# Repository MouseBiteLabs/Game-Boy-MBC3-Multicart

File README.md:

# Game Boy MBC3 Multicart

This is my design of a flashable MBC3-based multicart for the Game Boy. You can make a 2-in-1 or 4-in-1 cartridge, that changes games based on a button press or power cycling the Game Boy. With this board you can also make a single game, but with the addition of a pressable reset button on the cartridge.

The features are as follows:

- Able to make a cartridge with either 2x 2 MB games or 4x 1 MB games
- Adds a pressable button to the cartridge (no shell cutting required)
  - The button can be configured to cycle games on the cart, reset the console, or both
- Configurable to have separate save data for each game, or to share the same save data across multiple games
- Fully compatible with the <a href="https://www.gbxcart.com/">GBxCart RW</a> so you can transfer games and save files to and from the board

Some examples of fun cartridges you can make with this board are:
- A single Pokemon game that has a reset button
- Both Pokemon Gold and Silver with separate saves
- Both Pokemon Gold and Silver with *the same* save (save files are compatible between versions!)
- Both Pokemon Gold and Silver with *the same* save that can switch between versions *during gameplay without resetting* (hotswap!)
- A single copy of Mary-Kate and Ashley - Pocket Planner with two separate save files

All gerbers and source files can be found in this repo, as this project is fully open source. Technical documentation of the board can be found in the Technical folder.

## Tutorial Video

Here's a video companion to this repository, but you will still need to read the repo to complete the build.

")

## Important Things Before You Start

The most important thing to note is that SW2A MUST be in the OFF position. The board is still fully functional as long as you rely on the button inside the cartridge to switch games. **You cannot cycle games by turning the power on and off.** Details are below.

1) To use this board, you need to have an original Game Boy game that uses an MBC3 mapper chip. <a href="https://catskull.net/gb-rom-database/">You can find a list of games and their mappers here</a>. Use the search function. Please note the RAM is in bytes, not bits. Since SRAM in this repo is defined in bits, you need to convert by multiplying the number of bytes by 8.
2) You will need to remove the MBC3 from your donor cartridge for use on this board. This will require a hot air rework station or a hot plate. There's a list below of other parts you can re-use from the donor cartridge.
3) When soldering parts on, it's a good idea to put kapton tape or otherwise cover the bottom cartridge edge. You do not want to get solder on the cartridge contacts.
4) I am not responsible for any damage you do to your self or your property. Attempt this project at your own risk.
5) I do not guarantee design compatibility. You may encounter issues with certain games. There is also a chance I have made an error in the design or the BOM - if this is the case, I will do everything I can to address the problem as quickly as possible.
6) If you are using this board to make games other than for personal use, you must have permission from the originator to use and distribute any ROM images or other related material. You are responsible for making sure you adhere to any license requirements.

DO NOT use my circuit boards for profiting from stolen work - this especially includes homebrew content, ROM hacks, and using fan-made labels without permission from the originator. **Support original creators!**

## Board Characteristics and Order Information

The zipped folder contains all the gerber files for this board. The following options **must** be chosen when ordering boards for yourself.

- Thickness: 0.8mm
- Surface Finish: ENIG
- Gold Fingers: Yes, 30° chamfer

**Add this note to orders:** "The milling.gbr layer indicates where an unplated slot should be added to the board. Please add an unplated slot as indicated."

You can use the zipped folder at any board fabricator you like. You may also buy the board from PCBWay using this link (disclosure: I receive 10% of the sale value to go twoards future PCB orders of my own):

<a href="https://oshpark.com/shared_projects/9DCMXwOu">The board is also listed on OSH Park as well.</a> **Be sure to get them in 0.8mm thickness if you order from here.**

### Purchase from My Website

You can purchase this circuit board at my website, [https://mousebitelabs.store](https://mousebitelabs.store). Click the following image to be directed to the specific item listing:

### Purchase from Etsy

I also offer the board on Etsy, if you would rather purchase through there - click the banner to be redirected.

## Required Equipment

The EEPROMs on the board needs to be programmed somehow. I recommend using the GBxCart, as mentioned. These boards are fully compatible with it, and it makes reflashing games extremely easy using <a href="https://github.com/lesserkuma/FlashGBX">lesserkuma's FlashGBX software</a>.

Alternatively, you can buy an EEPROM programmer with a TSOP adapter. The downside to this method is that you have to desolder the chip every time you want to program it. The <a href="https://flashcatusb.com/">FlashcatUSB</a> is one popular option in retro spaces.

## Battery Safety

When assembling a board, I recommend populating all the parts *except* the battery, and getting it to run initially without it. This is to make it easier to fix any solder connections that might need fixing, without having to worry about getting the battery hot. And if you need to rework anything near the battery after you've put it on the board, be safe and remove it before putting a hot soldering iron next to it.

And this should go without saying, but if you're assembling these boards with a hot plate or hot air, *do not* solder the battery on this way. You should use an iron, and keep heat off of the battery as much as possible. 

(Also check polarity!)

## Board Configurations

There's a lot to cover here. There are four separate switches to configure, and two different sizes of SRAM to pick from. You also can add a real-time clock to the cartridge for games that needed it.

*Note that you can simply solder bridges from the middle pads of the switches to the left or right to the "ON" or "OFF" positions, instead of installing an actual switch.*

### Real-Time Clock (RTC)

If your game uses an RTC, populate C2, R2, X1, and Z1 as indicated in the BOM.

If your game does *not* use the RTC function, you can omit these parts, but you also need to bridge the pads of Z1 with solder.

### SRAM Size Selection

There are two sizes of SRAM you can use, and the type you use will dictate how your save data is stored on the cartridge and if it's shared between games or not.

- If you use a 1 Mbit SRAM (like the AS6C1008), then each game you put on the cartridge will have its own separate save files. If you program multiple copies of the same game, then you can effectively have multiple save files on the same cart. Easy example is Pokemon games - they only let you have one save file, but if you put Pokemon Red on the multicart four times, then that gives you four separate save files!
- If you use a 256 Kbit SRAM (like the AS6C62256) then all the games you put on the cartridge will *share* the same RAM space.  This feature is probably only useful for Pokemon games. As an example: this means that if you made a cart that has Pokemon Red and Blue on it, you would play both versions with the same save data, as save data between the two games are compatible with each other.

### Game Cycling Mode Switch (SW2)

SW2, split into two separate switches SW2A (bottom half) and SW2B (top half), controls how you change games/save data on the cartridge. The following table describes the different settings:

**DUE TO AN OVERLOOKED DATASHEET ERROR, SW2A *MUST* BE TURNED OFF. DO NOT USE IT IN THE "ON" POSITION.**

| Mode | SW2A (Bottom) | SW2B (Top) | Game change with reset? | Game change with button press? | Does the button reset? |
| ---- | ---------- | ------------- | ----------------------- | ------------------------------ | ---------------------- |
| 1    | OFF        | OFF           | No                      | Yes                            | Yes                    |
| 2    | OFF        | ON            | No                      | Yes                            | No                     |
|~~3~~ | ~~ON~~     | ~~OFF~~       | ~~Yes~~                 | ~~Yes~~                        | ~~Yes~~                |
|~~4~~ | ~~ON~~     | ~~ON~~        | ~~Yes~~                 | ~~No~~                         | ~~No~~                 |

The "game change" method in this table describes how you advance down the "game" columns described in the table for SW3.

### Game and Save Data Configuration Switch (SW3)

SW3, split into two separate switches SW3A (bottom half) and SW3B (top half), controls the order in which the ROM banks (the games) and the RAM banks (the save data) cycle. This table assumes you are using a 1 Mbit SRAM chip. If you are using a 256 Kbit SRAM, then every entry in the "RAM Banks" column can be described as "1x 256 Kbit", and all the "Game" columns will share that single RAM bank.

Please note that SW3A and SW3B are *different* than the SW3A and SW3B on the MBC5 Multicart PCB.

| Mode | SW3A (Top) | SW3B (Bottom) | ROM Banks  | RAM Banks   | Game 1     | Game 2     | Game 3     | Game 4     |
| ---- | ---- | ---- | ---------- | ----------- | ---------- | ---------- | ---------- | ---------- |
| A    | OFF  | ON   | 2x 2 MB    | 4x 256 Kbit | ROM1, RAM1 | ROM1, RAM2 | ROM2, RAM3 | ROM2, RAM4 |
| B    | OFF  | OFF  | 4x 1 MB    | 4x 256 Kbit | ROM1, RAM1 | ROM2, RAM2 | ROM3, RAM3 | ROM4, RAM4 |
| C    | ON   | ON   | 2x 2 MB    | 2x 256 Kbit | ROM1, RAM1 | ROM2, RAM2 |            |            |
| D    | ON   | OFF  | 2x 1 MB    | 2x 256 Kbit | ROM1, RAM1 | ROM2, RAM2 |            |            |

*Note: Mode D is useless. Just use Mode C instead.*

### Game Mode Examples

Here's a list of example cartridges you can make with these settings:
1) Pokemon Red, Blue, Yellow, and Green on one cartridge with separate save files that changes only via pressing the button, which also resets the game: **Mode 1B** with 1 Mbit SRAM
~~2) Pokemon Gold and Silver with separate save files that changes by pressing the button *or* cycling power on the Game Boy: **Mode 3C** with 1 Mbit SRAM~~
3) Pokemon Gold and Silver with the same save file that hotswaps when you press the button on the cartridge (changing games during gameplay): **Mode 2C** with 256 Kbit SRAM

## How to Program Games

When using the GBxCart to program multiple games to the cartridge, it's recommended to turn SW2A and SW2B to the OFF position. To change ROM/RAM banks to program, simply press the SW1 tactile button between programming steps. Using FlashGBX's "Refresh" button should show that the game information on the left of the screen changes after pressing the button.

If you're programming the flash chip separate from the board, you'll need to concatenate all the ROM files together into one large 4 MB file to program the chip with.

## Test Points and Final Checkout

On the back of the board are five test points. Here's where they are connected:

- TP1: SRAM supply voltage
- TP2: Battery voltage (after R1)
- TP3: Battery voltage (positive terminal of battery)
- TP4: Ground
- TP5: VCC input voltage

After you assemble your game, you should measure the current out of the battery. But first, you should program it with the GBxCart, or if you programmed the EEPROM separately, put it into a Game Boy and cycle power once. Then, flip the PCB upside down on a non-conductive surface (not your leg), and set your multimeter in DC millivolts (or volts). Put the positive probe on TP3 and the negative probe on TP2. If you used a 10kΩ for R1, as indicated in the BOM, you should read a voltage in the single or tens of millivolts for non-RTC games, or up to 60 mV for games using a real-time clock. If you have something much higher, especially voltages above 100mV, then you likely have an issue or short circuit on the board somewhere.

**Note: You need to power up the game at least once before battery currents will make sense - the battery management ICs can start up in an unknown state before applying main power to the board.**

To estimate battery life, see <a href="https://github.com/MouseBiteLabs/Game-Boy-MBC3-Cartridge/tree/main/Technical#estimating-battery-life">this section in the MBC3 Technical Design Document</a>, or for more in-depth analysis, <a href="https://hackaday.io/project/11864-tritiled/log/72554-determining-maximum-runtime-176-to-202-years-cr2032">this Hackaday post</a>.

### Current Draw Measurements and Battery Selection

The revision of MBC3 chip you are using will influence how much current draw you get, and thus how long your battery life will last. For the test set up, I am replacing the battery with a regulated DC power supply set for 3 VDC for consistency, on my regular MBC3 cart board with an MM1134 chip for U4, and brand new AS6C62256 SRAM.

These numbers are for reference only - to help you decide which MBC3 revision to use for your game, if you have a choice. These numbers are similar to a regular MBC3 cartridge, but the current required for retaining save data on the multicart will be slightly higher (about 0.2 uA) due to the extra components.

| Rev   | P/N      | Current draw (without RTC) | Battery Life Estimate (no RTC, CR2025) | Current draw (with RTC) | Battery Life Estimate (RTC, CR2025)  |
| ----- | -------- | -------------------------- | -------------------------------------- | ----------------------- | ------------------------------------ |
| MBC3A | LR38536B |          0.4 uA            |                47 years                |            1.7 uA       |               11 years               |
| MBC3A | BU3632K  |          0.7 uA            |                27 years                |            1.7 uA       |               11 years               |
| MBC3A | P-2      |          0.7 uA            |                27 years                |            4.1 uA       |               5 years                |
| MBC3B | BU3634K  |          0.8 uA            |                24 years                |            1.7 uA       |               11 years               |
| MBC3B | P-2      |          0.6 uA            |                31 years                |            3.9 uA       |               5 years                |

Here is the same table, but with AS6C1008 SRAM instead of AS6C62256. It draws approximately 1 uA more than the AS6C62256.

| Rev   | P/N      | Current draw (without RTC) | Battery Life Estimate (no RTC, CR2025) | Current draw (with RTC) | Battery Life Estimate (RTC, CR2025)  |
| ----- | -------- | -------------------------- | -------------------------------------- | ----------------------- | ------------------------------------ |
| MBC3A | LR38536B |          1.4 uA            |                13 years                |            2.7 uA       |               7 years                |
| MBC3A | BU3632K  |          1.7 uA            |                11 years                |            2.7 uA       |               7 years                |
| MBC3A | P-2      |          1.7 uA            |                11 years                |            5.1 uA       |               4 years                |
| MBC3B | BU3634K  |          1.8 uA            |                10 years                |            2.7 uA       |               7 years                |
| MBC3B | P-2      |          1.6 uA            |                12 years                |            4.9 uA       |               4 years                |

*If you have one of the revisions of MBC3 chips is missing from the table, please contact me!*

### Battery Size Considerations

The coin cells commonly used on Game Boy carts in order of increasing size are CR2016, CR2025, and CR2032. The CR2032 is the thickest, but yields the longest battery life.

Batteries that are as large as CR2032 will fit inside the shell, *however*, due to the thickness of the CR2032, using one makes it so the shell cannot be pressed down very easily. This makes the button inside the shell difficult to press reliably. For this reason, I recommend using the CR2025.

You should still be able to get 10+ years of battery life out of a CR2025 and a non-P-2 revision MBC3 chip. <a href="https://github.com/MouseBiteLabs/Game-Boy-MBC3-Cartridge/tree/main/Technical#estimating-battery-life">See this section in my main MBC3 repository for estimating battery life here.</a>

I haven't tested it, but I believe using battery holders instead of pre-tabbed batteries will similarly cause issues with trying to press the button in the middle of the cartridge.

### Why not FRAM?

This board is only suitable for using SRAM. One downside to SRAM, if you haven't figured it out yet, is that you need a battery to keep the SRAM powered on even when the game is turned off. So eventually the battery will die, and your save data is lost. Some people have used FRAM, or Ferroelectric RAM, to keep save data around even after the battery dies (specifically, the popular part that's used for FRAM carts is the FM18W08). But, using this FRAM chip has a handful of downsides, and the benefit of keeping save data after the battery dies *in my opinion* does not outweigh the cons, which are as follows:

1) Quality, new stock, 5V tolerant FRAM is expensive ($12+ per part).
2) Cheaper FRAM chips from eBay or Aliexpress are notoriously flaky (anecdotally, ~50% success rate).
3) FM18W08 maxes out at 256K (which is restrictive for multicarts).
4) FRAM memory access requires different chip select timing than SRAM, and the Game Boy expects SRAM, so it is not natively compatible with FRAM carts. The Gameboy Color specifically cannot (easily) be made to properly access FM18W08 chip. You *can* use an OR gate and add the CLK on the cart edge to try to achieve the necessary timing, but it only works (properly) for DMG/MGB/SGB, not the GBC. It usually *works* in practice for GBC, but it's technically a datasheet violation and can potentially cause issues in edge cases. <a href="https://github.com/Gekkio">(Thanks to gekkio for pointing this out!)</a>

Brand new SRAM chips are ~$3, and having the SRAM footprint also allows you to use SRAM from an original cart if desired. 

Note that this isn't to throw shade at any FRAM-based carts, but for me personally, it's more trouble than it's worth.

## Board Fitment

The shape of this board was originally meant to mimic original Game Boy circuit boards as closely as possible (v1.1 and earlier). Unfortunately, when placed in some aftermarket Game Boy cartridge shells (like those from Cloud Game Store), the circuit board has a lot of freedom to rotate around the main screw hole in the bottom-middle of the cartridge. This can cause misalignment when you put it in a Game Boy, which can cause a game to either not load properly (garbled Game Boy logo) or shut off the Game Boy because of a short circuit. This isn't *dangerous* or anything, just annoying.

In order to make the boards fit nicer in any kind of shell, for v1.4 I added extended tabs of circuit board material to the edges of the cartridges to keep it from rotating too much in shells, which was suggested to me by <a href="https://github.com/orangeglo">orangeglo</a>! (Thanks!)

If you're having trouble fitting the circuit board into a shell, because the tabs interfere with the cart edges, you can safely sand or trim them down as there is no copper within the tabs themselves. The only shell that appears to require any kind of trimming are Kitsch-Bent shells.

## Bill of Materials (BOM)

*Please note that there was an error in the published BOM before February 24, 2024. If you assembled your board before that date, I recommend you replace R5, R6, and C8 to their new values listed below.*

| Reference Designators | Value/Part Number      | Package        | Description        | Source                                           |
| --------------------- | ---------------------- | -------------- | ------------------ | ------------------------------------------------ |
| B1                    | CR2025, CR2016, CR2032*| See note above | Backup Battery     | [https://mou.sr/3PLccol](https://mou.sr/3PLccol) |
| C1                    | 0.1uF                  | 0603           | Capacitor (MLCC)   | [https://mou.sr/3ENc15O](https://mou.sr/3ENc15O) |
| C2                    | 15 pF                  | 0603           | Capacitor (MLCC)   | [https://mou.sr/3PPorjO](https://mou.sr/3PPorjO) |
| Z1                    | 15 pF                  | 0603           | Capacitor (MLCC)   | [https://mou.sr/3PPorjO](https://mou.sr/3PPorjO) |
| C4                    | 0.1uF                  | 0603           | Capacitor (MLCC)   | [https://mou.sr/3ENc15O](https://mou.sr/3ENc15O) |
| C5                    | 0.1uF                  | 0603           | Capacitor (MLCC)   | [https://mou.sr/3ENc15O](https://mou.sr/3ENc15O) |
| C6                    | 10uF                   | 0603           | Capacitor (MLCC)   | [https://mou.sr/3mZtSkF](https://mou.sr/3mZtSkF) |
| C7                    | 0.1uF                  | 0603           | Capacitor (MLCC)   | [https://mou.sr/3ENc15O](https://mou.sr/3ENc15O) |
| C8                    | 0.01uF                 | 0603           | Capacitor (MLCC)   | [https://mou.sr/3AsRwK1](https://mou.sr/3AsRwK1) |
| Q1                    | 2N7002                 | SOT-23         | N-Channel FET      | [https://mou.sr/3rgfh6J](https://mou.sr/3rgfh6J) |
| R1                    | 10k                    | 0603           | Resistor           | [https://mou.sr/3riR7IH](https://mou.sr/3riR7IH) |
| R2                    | 330k                   | 0603           | Resistor           | [https://mou.sr/3PZ2pvj](https://mou.sr/3PZ2pvj) |
| R5                    | 130k                   | 0603           | Resistor           | [https://mou.sr/3MjXliy](https://mou.sr/3MjXliy) |
| R6                    | 130k                   | 0603           | Resistor           | [https://mou.sr/3MjXliy](https://mou.sr/3MjXliy) |
| R8                    | 10k                    | 0603           | Resistor           | [https://mou.sr/3riR7IH](https://mou.sr/3riR7IH) |
| R9                    | 130k                   | 0603           | Resistor           | [https://mou.sr/3MjXliy](https://mou.sr/3MjXliy) |
| R10                   | 49.9k                  | 0603           | Resistor           | [https://mou.sr/3Q3NRZO](https://mou.sr/3Q3NRZO) |
| SW1                   | See note               | 5.2 x 5.2mm    | Tactile Switch     | See Note |
| SW2                   | CAS-D20TA              | J Form Lead    | Dual SPDT          | [https://mou.sr/44YZNT5](https://mou.sr/44YZNT5) |
| SW3                   | CAS-D20TA              | J Form Lead    | Dual SPDT          | [https://mou.sr/44YZNT5](https://mou.sr/44YZNT5) |
| U1                    | 29F032, 29F033         | TSOP-40        | Flash EEPROM       | AliExpress or eBay                               |
| U2                    | MBC3A or MBC3B         | QFP-32         | MBC3 Mapper        | Donor MBC3 Game Boy cartridge                    |
| U3                    | AS6C62256, AS6C1008    | SOP-28, SOP-32 | SRAM               | [https://mou.sr/3sFegFF](https://mou.sr/3sFegFF) |
| U4                    | TPS3613                | MSOP-10        | Battery Management | [https://mou.sr/45Ir2kh](https://mou.sr/45Ir2kh) |
| U5                    | SN74HCS74              | TSSOP-14       | Dual Flip Flop     | [https://mou.sr/3QYGEuT](https://mou.sr/3QYGEuT) |
| U6                    | SN74AHC1G126           | SC70           | Tri-State Buffer   | [https://mou.sr/3T9Zdim](https://mou.sr/3T9Zdim) |
| U7                    | SN74AHC1G126           | SC70           | Tri-State Buffer   | [https://mou.sr/3T9Zdim](https://mou.sr/3T9Zdim) |
| U8                    | SN74AHC1G126           | SC70           | Tri-State Buffer   | [https://mou.sr/3T9Zdim](https://mou.sr/3T9Zdim) |
| X1                    | 32.768 kHz             | Radial         | Crystal Oscillator | [https://mou.sr/3ZteKuy](https://mou.sr/3ZteKuy) |

### Note about SW1

If SW1 is long enough, it will sit inside the shell in a way that lets you press it by lightly pressing on the cartridge shell. This way, you can activate it without removing it from the console. You need to find a switch that has an extended stem on AliExpress, eBay, or Amazon (**if you find a compatible switch on Mouser or Digikey, please let me know**). The measurements will be 5.2 mm x 5.2 mm, with a height of 3.5 mm. Sometimes these parts are listed as "4 mm x 4 mm" or "5 mm x 5 mm" instead. Check the datasheet, if available, to see if it'll fit the footprint. They should have listing pictures similar to the ones seen here:

### Note about SW2, SW3

Instead of using the somewhat pricey switch designated for SW2 and SW3, you can instead just bridge the pads with solder from the middle pad to the pad in the direction you want to set the switch to. For example - in the below picture, SW3A and SW3B are both in the "ON" position in both cases. (Note that the white switches on the right image are switched to the right.)

**REMINDER: SW2A MUST BE IN THE OFF POSITION.**

### Note about MBC3 Revisions

If you have a choice, I recommend against using the original revision-less MBC3 mapper for this specific circuit board. You should use an MBC3A or MBC3B if possible. Save the revision-less MBC3 chips for regular MBC3 cartridges!

*[Images of MBC3 chips from <a href="https://gbhwdb.gekkio.fi/cartridges/mbc3.html">Game Boy Hardware Database</a>.]*

### Usable Donor Cartridge Parts

You can use a few parts from the donor cart on the new board to save some money. Note that you will generally get better reliability with new parts as opposed to old ones. For example: I have seen failed RAM chips from donors in the past.

1) **C2, R2, X1, Z1: RTC Components** - You can move over these parts if you're using the real-time clock function. Note that Z1 and C2 are designated as C2 and C3 on my board. They're the same value, so they're interchangeable.
2) **U2: MBC3A or MBC3B** - This one is required
3) **U3: SRAM** - You can use this part *only if* the sum of the RAM space for the games you're using is the same or less amount of RAM that the donor cartridge has. If you plan to have separate save data for every game, you'll probably need to buy an AS6C1008.

You could probably transfer over most of the 0.1uF capacitors but they're pretty cheap anyway, so I generally just recommend buying new resistors and capacitors.

## Things to Remember

- The 29F032 and 29F033 have been known to occasionally be defective upon arrival. They're either used, or new old stock, and usually only available from AliExpress.
- The footprint for the battery can fit a CR2032, CR2025, or CR2016 with solder tabs. The only difference is the mAh capacity (larger number = longer life). If you get Panasonic tabbed batteries, you may have to trim the battery tabs to make them fit on the footprint.
- Generally, ROM sizes are conveyed in terms of kilobytes and megabytes (KB, MB). RAM size is usually conveyed in terms of kilobits or megabits (Kbit, Mbit). You can convert Kbit and Mbit to KB and MB by dividing Kbit or Mbit by 8. For example, 256 Kbit = 32 KB.

## Labels

If you want a Bucket Mouse branded label for your cartridge, look no further than <a href="https://krizdingus.com/mousebitelabs/">krizdingus's designs</a>. Special thanks to Kris for designing these, they look awesome! (If you are going to order/print these, use the high-res images hosted on his website, and *keep the labels for personal or non-commercial use only.*)

## Why does SW2A need to be OFF?

SW2A in the ON position previously allowed the multicart to swap games whenever you power cycled the Game Boy. This was achieved by connecting the /RST line on the Game Boy to the CLK input on the flip-flop. The /RST line was held low when power was off by the RESET output of the TPS3613 battery management IC driving the gate of a FET.

The datasheet says this output is a push-pull output, and implies it will behave normally when power is off and the battery is being relied on for power. However, that is not the behavior I have later found to be true. Instead, if the voltage on the VDD pin is too low (like when the power is turned off), this RESET output floats. This causes the FET to not be asserted, and then allows the /RST line to float.

In Modes 3 or 4, where SW2A is in the ON position, /RST is connected to the flip-flop's CLK input. If /RST floats, then CLK floats, which can cause excess current draw from the flip-flop, draining the battery much faster than expected. Therefore, it is recommended to ONLY use a button to change games, and not to rely on power cycling.

A new board to replace this design with something more suitable will be completed in the future. In the meantime, *do not put SW2A in the ON position.*

## Revision History

### v1.3
- Fixed debounce circuit for push button
- Adjusted board edge tabs to better fit in shells

### v1.2
- Changed C3 to Z1
- Added nubs on the board edge to prevent the circuit board from rattling around in aftermarket cartridges

### v1.1
- Fix schematic errors
- Extended cart edge down by 0.25 mm for better fitment
- Added OSHW logo and "SUPPORT ORIGINAL CREATORS!"

### v1.0
- Prototype revision

## Resources and Acknowledgements

- <a href="http://www.devrs.com/gb/files/hardware.html">Jeff Frohwein's GameBoy Tech Page</a>
- <a href="https://gbhwdb.gekkio.fi/">Game Boy Hardware Database</a>
- <a href="https://catskull.net/gb-rom-database/">Nintendo Gameboy Game List</a>
- <a href="https://www.gbxcart.com/">insideGadgets discord server for GBxCart RW compatibility requirements</a>
- <a href="https://github.com/lesserkuma/FlashGBX">Lesserkuma's FlashGBX software</a>
- <a href="https://www.ti.com/lit/ds/symlink/tps3613-01.pdf?HQS=dis-mous-null-mousermode-dsf-pf-null-wwe&ts=1698238885366&ref_url=https%253A%252F%252Feu.mouser.com%252F">TPS3613 Datasheet</a>
- Board outline modified from <a href="https://tinkerer.us/projects/homebrew-gameboy-cartridge.html">Dillon Nichols's Homebrew Gameboy Cartridge project</a>
- Thanks to <a href="https://github.com/orangeglo">orangeglo</a> for his suggestion of adding spacers around the board edge for better fitment in aftermarket cartridges
- Some components from <a href="https://github.com/adafruit/Adafruit-Eagle-Library">Adafruit's Eagle parts library</a>
- Some components from <a href="https://www.snapeda.com/">SnapMagic</a>
- Thank you to <a href="https://github.com/Gekkio">gekkio</a> for their deep Game Boy knowledge resources, and for collaboration in demystifying some of the design choices on Game Boy cartridges
- Thanks to the awesome members of the <a href="https://moddedgameboy.club/">Modded Gameboy Club</a> for their feedback and support during the entire project development

## License

<br />This work is licensed under a <a rel="license" href="http://creativecommons.org/licenses/by-sa/4.0/">Creative Commons Attribution-ShareAlike 4.0 International License</a>. You are able to copy and redistribute the material in any medium or format, as well as remix, transform, or build upon the material for any purpose (even commercial) - but you **must** give appropriate credit, provide a link to the license, and indicate if any changes were made.

©MouseBiteLabs 2023

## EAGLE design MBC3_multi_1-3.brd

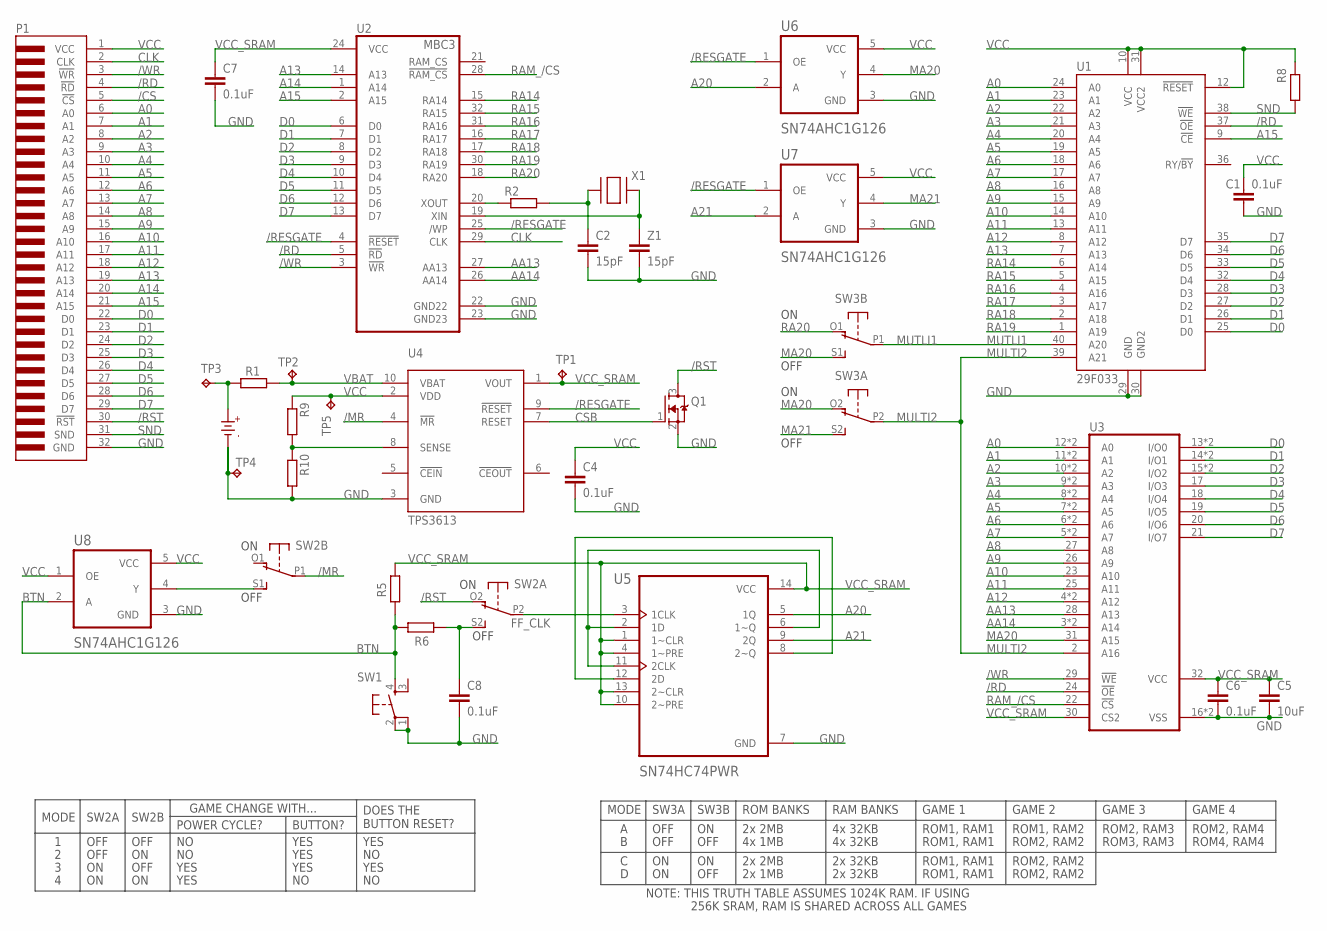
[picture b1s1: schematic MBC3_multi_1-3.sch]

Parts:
C1, C4, C6, C7, C8: 0.1uF; C0603
C2: 15pF; C0603
C5: 10uF; C0603
P1: GBC_CARTTAB; GBC_CART_TABBED
Q1: 2N7002; SOT23
R1, R2, R5, R6, R8, R9, R10: RR0603; R0603
SW1: SPST_TACT-KMR2; KMR2
SW2, SW3: SPDT-2S; CAS-D20A
TP1, TP2, TP3, TP4, TP5: TPB1,27; B1,27
U1: 29F033; TSOP-40
U2: MBC3; QFP-32
U3: 1008_62256_SRAM; SOP-32L
U4: TPS3613; MSOP-10
U5: SN74HC74PWR; SOP65P640X120-14N
U6, U7, U8: SN74AHC1G126; SC70
U$7: CR2025
X1: XTAL-3.2X1.5; XTAL3215
Z1: 15pF; C0603

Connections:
/CS: P1.5 (!CS)
/MR: SW2.P1, U4.4 (!MR)
/RD: P1.4 (!RD), U1.37 (!OE), U2.5 (!RD), U3.24 (!OE)
/RESGATE: U2.4 (!RESET), U2.25 (/WP), U4.9 (!RESET), U6.1 (OE), U7.1 (OE)
/RST: P1.30 (!RST), Q1.3 (D), SW2.O2 (O)
/WR: P1.3 (!WR), U2.3 (!WR), U3.29 (!WE)
A0: P1.6 (A0), U1.24 (A0), U3.12 (A0), U3.L12 (A0)
A1: P1.7 (A1), U1.23 (A1), U3.11 (A1), U3.L11 (A1)
A2: P1.8 (A2), U1.22 (A2), U3.10 (A2), U3.L10 (A2)
A3: P1.9 (A3), U1.21 (A3), U3.9 (A3), U3.L9 (A3)
A4: P1.10 (A4), U1.20 (A4), U3.8 (A4), U3.L8 (A4)
A5: P1.11 (A5), U1.19 (A5), U3.7 (A5), U3.L7 (A5)
A6: P1.12 (A6), U1.18 (A6), U3.6 (A6), U3.L6 (A6)
A7: P1.13 (A7), U1.17 (A7), U3.5 (A7), U3.L5 (A7)
A8: P1.14 (A8), U1.16 (A8), U3.27 (A8)
A9: P1.15 (A9), U1.15 (A9), U3.26 (A9)
A10: P1.16 (A10), U1.14 (A10), U3.23 (A10)
A11: P1.17 (A11), U1.13 (A11), U3.25 (A11)
A12: P1.18 (A12), U1.8 (A12), U3.4 (A12), U3.L4 (A12)
A13: P1.19 (A13), U1.7 (A13), U2.14 (A13)
A14: P1.20 (A14), U2.1 (A14)
A15: P1.21 (A15), U1.9 (!CE), U2.2 (A15)
A20: U5.5 (1Q), U6.2 (A)
A21: U5.9 (2Q), U7.2 (A)
AA13: U2.27 (AA13), U3.28 (A13)
AA14: U2.26 (AA14), U3.3 (A14), U3.L3 (A14)
BTN: R5.2, R6.1, SW1.4 (S), U8.2 (A)
CLK: P1.2 (CLK), U2.29 (CLK)
CSB: Q1.1 (G), U4.7 (RESET)
D0: P1.22 (D0), U1.25 (D0), U2.6 (D0), U3.13 (I/O0), U3.L13 (I/O0)
D1: P1.23 (D1), U1.26 (D1), U2.7 (D1), U3.14 (I/O1), U3.L14 (I/O1)
D2: P1.24 (D2), U1.27 (D2), U2.8 (D2), U3.15 (I/O2), U3.L15 (I/O2)
D3: P1.25 (D3), U1.28 (D3), U2.9 (D3), U3.17 (I/O3)
D4: P1.26 (D4), U1.32 (D4), U2.10 (D4), U3.18 (I/O4)
D5: P1.27 (D5), U1.33 (D5), U2.11 (D5), U3.19 (I/O5)
D6: P1.28 (D6), U1.34 (D6), U2.12 (D6), U3.20 (I/O6)
D7: P1.29 (D7), U1.35 (D7), U2.13 (D7), U3.21 (I/O7)
FF_CLK: SW2.P2, U5.3 (1CLK)
GND: C1.2, C2.2, C4.2, C5.2, C6.2, C7.2, C8.2, P1.32 (GND), Q1.2 (S), R10.2, SW1.1, SW1.2, TP4.TP, U1.29 (GND), U1.30 (GND2), U2.22 (GND22), U2.23 (GND23), U3.16 (VSS), U3.L16 (VSS), U4.3 (GND), U5.7 (GND), U6.3 (GND), U7.3 (GND), U8.3 (GND), U$7.-, Z1.2
MA20: SW3.O2 (O), SW3.S1 (S), U3.31 (A15), U6.4 (Y)
MA21: SW3.S2 (S), U7.4 (Y)
MULTI2: SW3.P2, U1.39 (A21), U3.2 (A16)
MUTLI1: SW3.P1, U1.40 (A20)
unnamed: C8.1, R6.2, SW2.S2 (S)
unnamed: SW2.S1 (S), U8.4 (Y)
unnamed: R1.2, TP3.TP, U$7.+
unnamed: U5.2 (1D), U5.6 (1~Q), U5.11 (2CLK)
unnamed: R2.1, U2.20 (XOUT)
unnamed: C2.1, R2.2, X1.P$2
unnamed: U2.19 (XIN), X1.P$1, Z1.1
unnamed: R9.2, R10.1, U4.8 (SENSE)
unnamed: U5.8 (2~Q), U5.12 (2D)
RA14: U1.6 (A14), U2.15 (RA14)
RA15: U1.5 (A15), U2.32 (RA15)
RA16: U1.4 (A16), U2.31 (RA16)
RA17: U1.3 (A17), U2.16 (RA17)
RA18: U1.2 (A18), U2.17 (RA18)
RA19: U1.1 (A19), U2.30 (RA19)
RA20: SW3.O1 (O), U2.18 (RA20)
RAM_/CS: U2.28 (!RAM_CS), U3.22 (!CS)
SND: P1.31 (SND), R8.2, U1.38 (!WE)
VBAT: R1.1, TP2.TP, U4.10 (VBAT)
VCC: C1.1, C4.1, P1.1 (VCC), R8.1, R9.1, TP5.TP, U1.10 (VCC), U1.12 (!RESET), U1.31 (VCC2), U4.2 (VDD), U6.5 (VCC), U7.5 (VCC), U8.1 (OE), U8.5 (VCC)
VCC_SRAM: C5.1, C6.1, C7.1, R5.1, TP1.TP, U2.24 (VCC), U3.30 (CS2), U3.32 (VCC), U4.1 (VOUT), U5.1 (1~CLR), U5.4 (1~PRE), U5.10 (2~PRE), U5.13 (2~CLR), U5.14 (VCC)

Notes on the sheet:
OFF
SW3A
SW3B
ROM BANKS
RAM BANKS
4x 1MB
4x 32KB
2x 1MB
2x 2MB
2x 32KB
GAME 1
GAME 2
GAME 3
GAME 4
ROM1, RAM1
ROM2, RAM2
ROM3, RAM3
ROM4, RAM4
ROM1, RAM2
ROM2, RAM3
ROM2, RAM4
NOTE: THIS TRUTH TABLE ASSUMES 1024K RAM. IF USING
256K SRAM, RAM IS SHARED ACROSS ALL GAMES
MODE
SW2A
SW2B
POWER CYCLE?
DOES THE BUTTON RESET?
YES
BUTTON?
GAME CHANGE WITH...

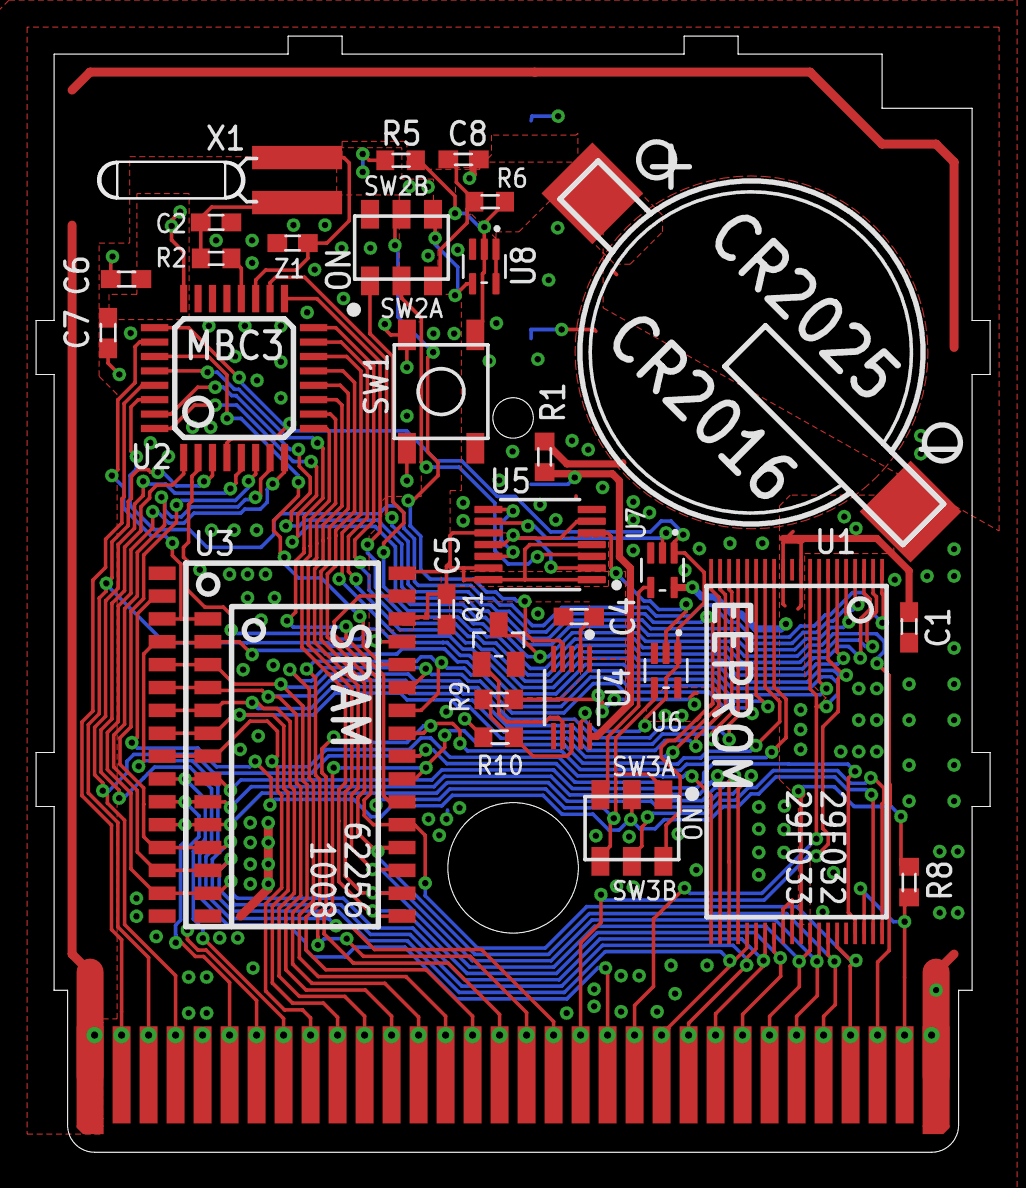
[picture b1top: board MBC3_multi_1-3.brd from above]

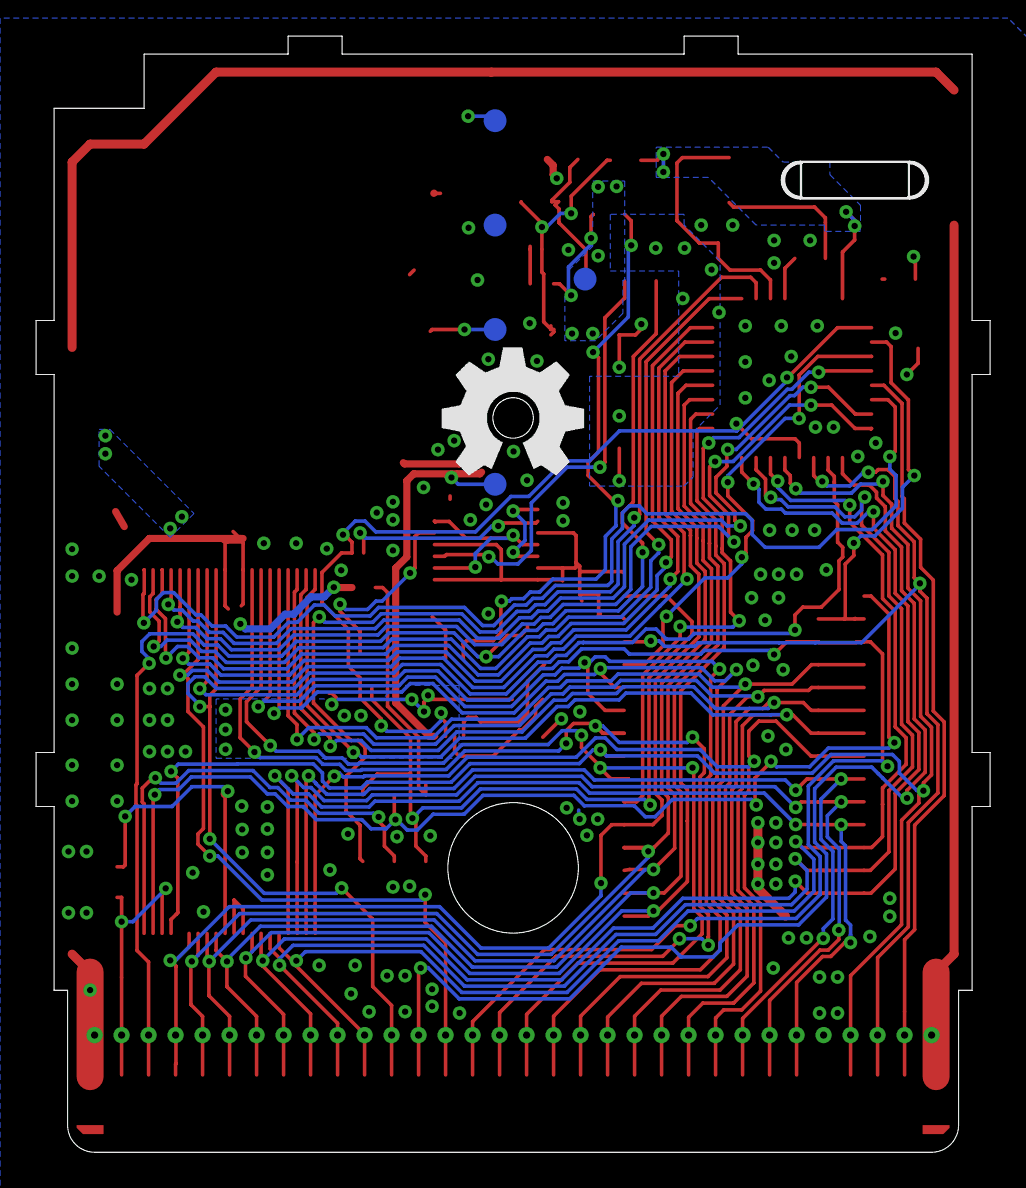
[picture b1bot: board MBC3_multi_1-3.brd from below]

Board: 2 copper layers, 53.0 x 62.0 mm, 35 parts (5 on the bottom side), 63 nets.

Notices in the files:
README.md:
This work is licensed under a Creative Commons Attribution-ShareAlike 4.0 International License. You are able to copy and redistribute the material in any medium or format, as well as remix, transform, or build upon the material for any purpose (even commercial) - but you **must** give appropriate credit, provide a link t
©MouseBiteLabs 2023
